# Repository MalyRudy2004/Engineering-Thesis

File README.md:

# Development of a fiber optic system for spatial localization of a person in a room

### Engineering Thesis
**Author:** Piotr Łuczak  
**Student ID:** 246965  
 
---

## 📄 Full Text / Thesis Document
The complete text of the engineering thesis (PDF) can be downloaded here:
[Piotr_Łuczak_Development_of_a_fiber_optic_system_for_spatial_localization_of_a_person_in_a_room.pdf](Piotr_Łuczak_Development_of_a_fiber_optic_system_for_spatial_localization_of_a_person_in_a_room.pdf)

---

## Project Overview
This repository contains all the necessary files to understand, recreate, and further develop the project presented in the engineering thesis. The system utilizes fiber-optic microbending sensors to detect and localize human presence in a room.

## Repository Contents

The repository is organized into the following main sections:

- **Python Application** PC software for real-time visualization of the object's position (GUI).

- **STM32 Firmware** Full `STM32CubeIDE` project for the **STM32F303K8** microcontroller. Contains source code, drivers, and logic implementation.

- **KiCad Design Files** Complete hardware design including:
  - Schematics (`.kicad_sch`)
  - PCB Layout (`.kicad_pcb`)
  - **Component Libraries:** Project-specific schematic symbols, footprints, and 3D models of the components used.

- **Datasheets** Technical documentation for key components used in the project (Laser Drivers, MOSFETs, Photodiodes, etc.).

---

## Important Hardware Disclaimer

**Please read before reproducing the PCB:**

There is a discrepancy in the STM32 pin connections between the KiCad schematics and the STM32CubeIDE project configuration. 

- The connection on the physical PCB was **corrected manually after production** (hardware patch).
- **The correct pinout** is defined and explained in the STM32 Project source code.
- Please refer specifically to the **GPIO library header file** for the verified and working pin configuration.

---
*Politechnika Łódzka (Lodz University of Technology) - 2026*

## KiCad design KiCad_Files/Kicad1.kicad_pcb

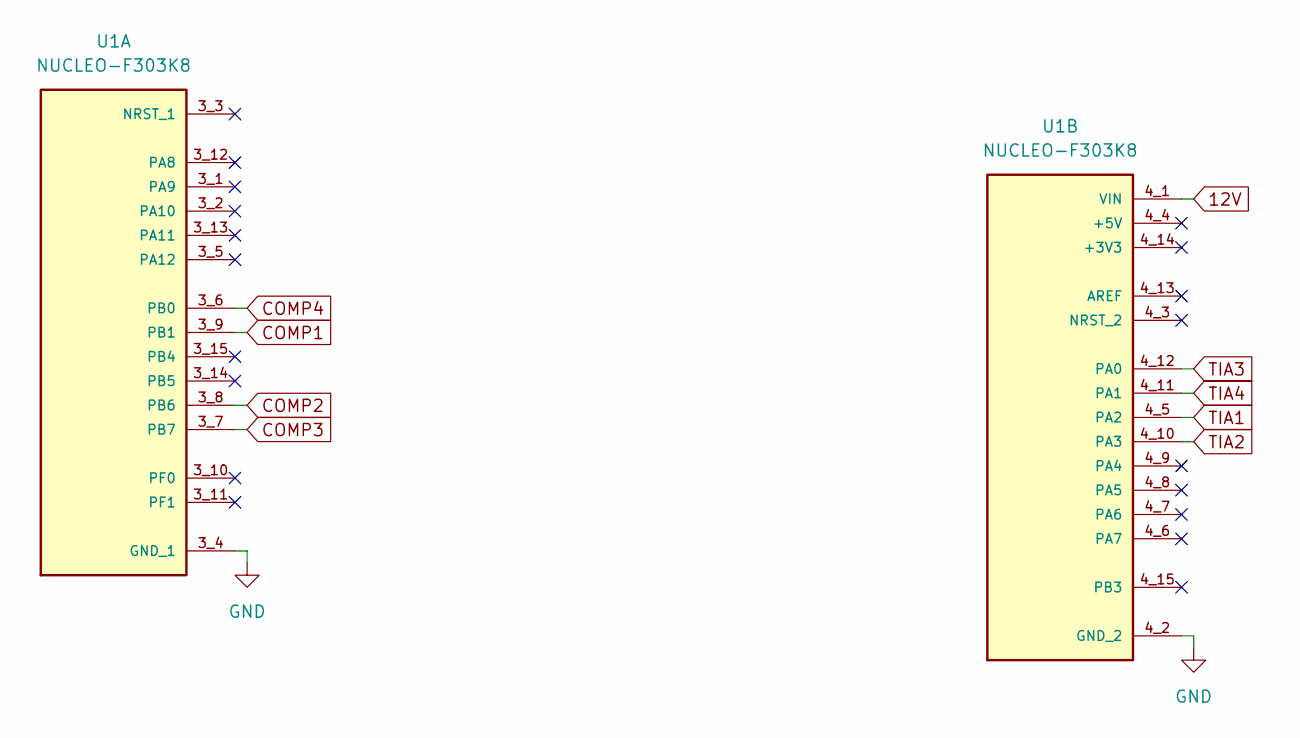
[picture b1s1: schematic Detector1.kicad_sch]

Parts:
U1: NUCLEO-F303K8; MODULE_NUCLEO-F303K8; PARTREV 5

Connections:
12V: U1.4_1 (VIN); also elsewhere on the board
COMP1: U1.3_9 (PB1); also elsewhere on the board
COMP2: U1.3_8 (PB6); also elsewhere on the board
COMP3: U1.3_7 (PB7); also elsewhere on the board
COMP4: U1.3_6 (PB0); also elsewhere on the board
GND: U1.3_4 (GND_1), U1.4_2 (GND_2); also elsewhere on the board
TIA1: U1.4_5 (PA2); also elsewhere on the board
TIA2: U1.4_10 (PA3); also elsewhere on the board
TIA3: U1.4_12 (PA0); also elsewhere on the board
TIA4: U1.4_11 (PA1); also elsewhere on the board

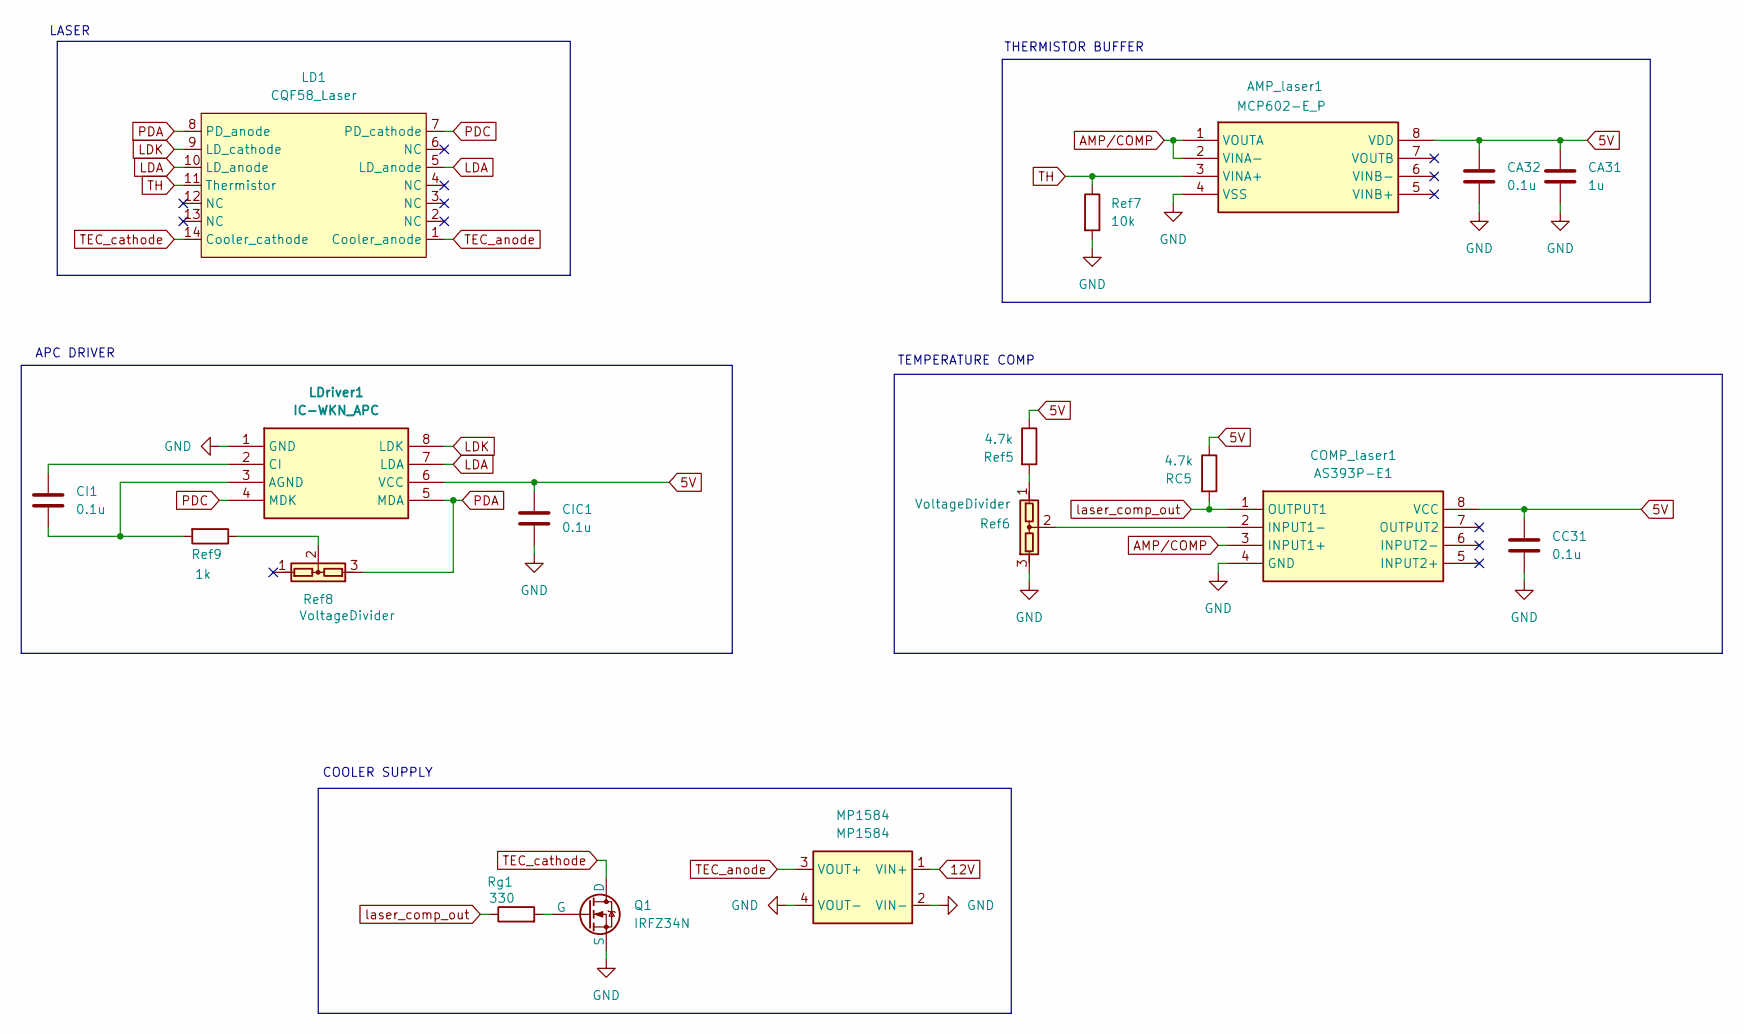
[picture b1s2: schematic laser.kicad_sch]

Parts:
AMP_laser1: MCP602-E_P; DIP781W56P254L950H533Q8N; Manufacturer_Part_Number MCP602-E/P; Mouser Part Number 579-MCP602-E/P
CA31: 1u; C_Radial_D5.0mm_H11.0mm_P2.00mm
CA32: 0.1u; C_Disc_D5.0mm_W2.5mm_P2.50mm
CC31: 0.1u; C_Disc_D5.0mm_W2.5mm_P2.50mm
CI1: 0.1u; C_Disc_D5.0mm_W2.5mm_P2.50mm
CIC1: 0.1u; C_Disc_D5.0mm_W2.5mm_P2.50mm
COMP_laser1: AS393P-E1; DIP762W56P254L930H431Q8N; Manufacturer_Part_Number AS393P-E1; Mouser Part Number 621-AS393P-E1
LD1: CQF58_Laser; CQ58F
LDriver1: IC-WKN_APC; IC-wkn; Manufacturer_Part_Number IC-WKNSOP8
MP1584: MP1584; mp1584
Q1: IRFZ34N
RC5: 4.7k; R_Axial_DIN0207_L6.3mm_D2.5mm_P10.16mm_Horizontal
Ref5: 4.7k; R_Axial_DIN0207_L6.3mm_D2.5mm_P10.16mm_Horizontal
Ref6, Ref8: VoltageDivider; Potentiometer_ACP_CA9-V10_Vertical
Ref7: 10k; R_Axial_DIN0207_L6.3mm_D2.5mm_P10.16mm_Horizontal
Ref9: 1k; R_Axial_DIN0207_L6.3mm_D2.5mm_P10.16mm_Horizontal
Rg1: 330; R_Axial_DIN0207_L6.3mm_D2.5mm_P10.16mm_Horizontal

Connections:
5V: AMP_laser1.8 (VDD), CA31.1, CA32.1, CC31.1, CIC1.1, COMP_laser1.8 (VCC), LDriver1.6 (VCC), RC5.1, Ref5.1; also elsewhere on the board
12V: MP1584.1 (VIN+); also elsewhere on the board
AMP/COMP: AMP_laser1.1 (VOUTA), AMP_laser1.2 (VINA-), COMP_laser1.3 (INPUT1+)
GND: AMP_laser1.4 (VSS), CA31.2, CA32.2, CC31.2, CIC1.2, COMP_laser1.4 (GND), LDriver1.1 (GND), MP1584.2 (VIN-), MP1584.4 (VOUT-), Q1.3 (S), Ref6.3, Ref7.2; also elsewhere on the board
LDA: LD1.5 (LD_anode), LD1.10 (LD_anode), LDriver1.7 (LDA)
LDK: LD1.9 (LD_cathode), LDriver1.8 (LDK)
unnamed: COMP_laser1.2 (INPUT1-), Ref6.2
unnamed: CI1.2, LDriver1.3 (AGND), Ref9.2
unnamed: CI1.1, LDriver1.2 (CI)
unnamed: Q1.2 (G), Rg1.2
unnamed: Ref5.2, Ref6.1
unnamed: Ref8.2, Ref9.1
PDA: LD1.8 (PD_anode), LDriver1.5 (MDA), Ref8.3
PDC: LD1.7 (PD_cathode), LDriver1.4 (MDK)
TEC_anode: LD1.1 (Cooler_anode), MP1584.3 (VOUT+)
TEC_cathode: LD1.14 (Cooler_cathode), Q1.1 (D)
TH: AMP_laser1.3 (VINA+), LD1.11 (Thermistor), Ref7.1
laser_comp_out: COMP_laser1.1 (OUTPUT1), RC5.2, Rg1.1

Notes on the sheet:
COOLER SUPPLY
APC DRIVER
TEMPERATURE COMP
LASER
THERMISTOR BUFFER

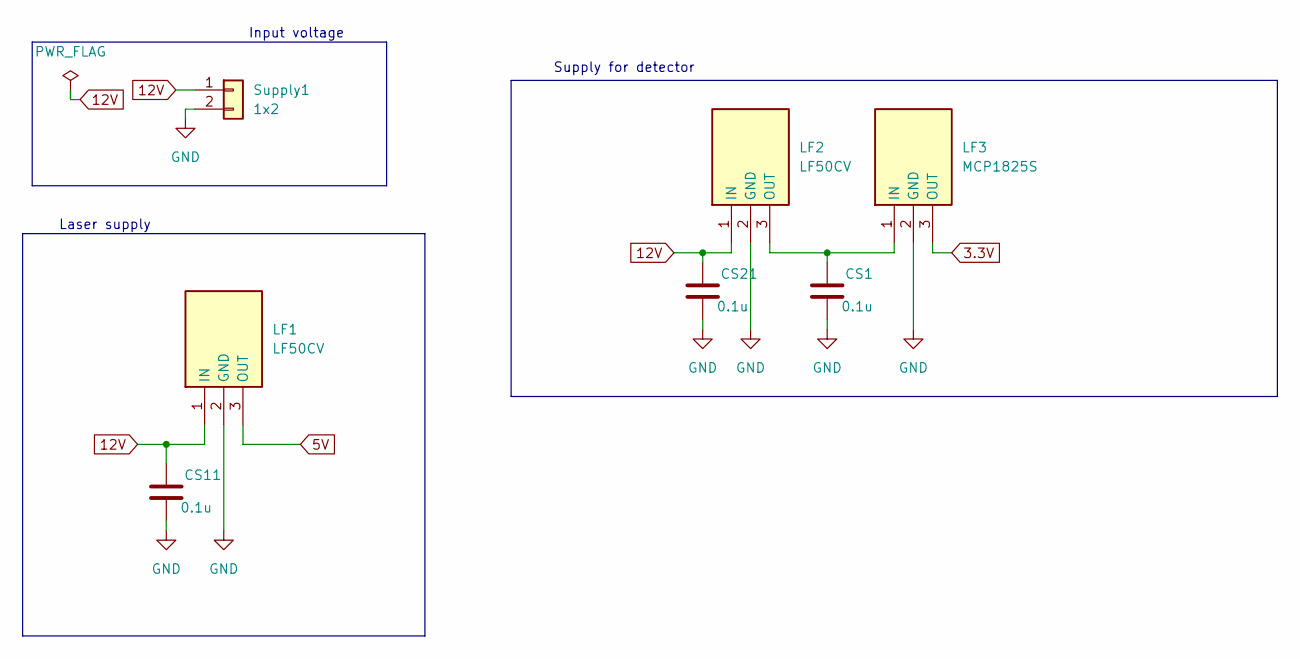
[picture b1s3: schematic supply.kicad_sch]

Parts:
CS1, CS11, CS21: 0.1u; C_Disc_D5.0mm_W2.5mm_P2.50mm
LF1, LF2: LF50CV; TO-220-3_Vertical; Manufacturer_Part_Number LF50CV; Mouser Part Number 511-LF50CV
LF3: MCP1825S; TO-220-3_Vertical; Manufacturer_Part_Number LF50CV; Mouser Part Number 511-LF50CV
Supply1: 1x2; PinHeader_1x02_P2.54mm_Vertical

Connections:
3.3V: LF3.3 (OUT); also elsewhere on the board
5V: LF1.3 (OUT); also elsewhere on the board
12V: CS11.1, CS21.1, LF1.1 (IN), LF2.1 (IN), Supply1.1; also elsewhere on the board
GND: CS1.2, CS11.2, CS21.2, LF1.2 (GND), LF2.2 (GND), LF3.2 (GND), Supply1.2; also elsewhere on the board
unnamed: CS1.1, LF2.3 (OUT), LF3.1 (IN)

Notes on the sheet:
Input voltage
Supply for detector
Laser supply

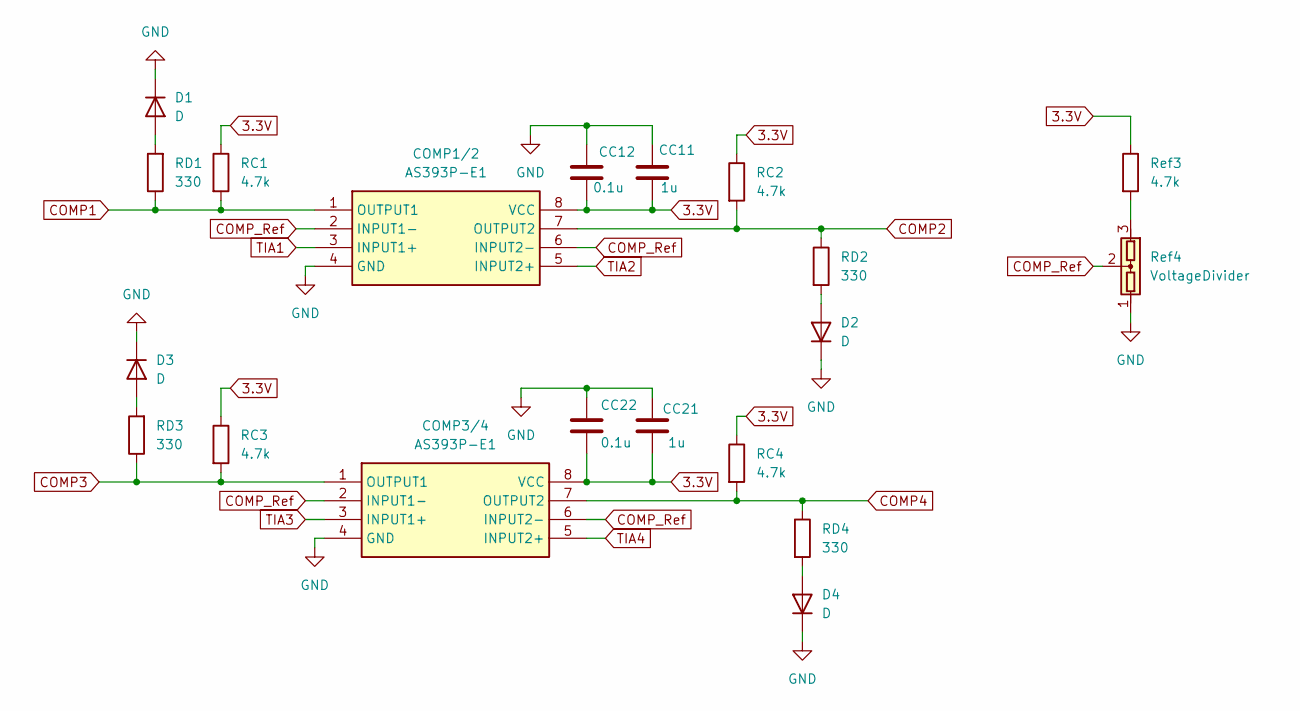
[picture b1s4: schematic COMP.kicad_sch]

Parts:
CC11, CC21: 1u; C_Radial_D5.0mm_H11.0mm_P2.00mm
CC12, CC22: 0.1u; C_Disc_D5.0mm_W2.5mm_P2.50mm
COMP1/2, COMP3/4: AS393P-E1; DIP762W56P254L930H431Q8N; Manufacturer_Part_Number AS393P-E1; Mouser Part Number 621-AS393P-E1
D1, D2, D3, D4: D; LED_D5.0mm
RC1, RC2, RC3, RC4: 4.7k; R_Axial_DIN0207_L6.3mm_D2.5mm_P10.16mm_Horizontal
RD1, RD2, RD3, RD4: 330; R_Axial_DIN0207_L6.3mm_D2.5mm_P10.16mm_Horizontal
Ref3: 4.7k; R_Axial_DIN0207_L6.3mm_D2.5mm_P10.16mm_Horizontal
Ref4: VoltageDivider; Potentiometer_ACP_CA9-V10_Vertical

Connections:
3.3V: CC11.2, CC12.2, CC21.2, CC22.2, COMP1/2.8 (VCC), COMP3/4.8 (VCC), RC1.1, RC2.1, RC3.1, RC4.1, Ref3.1; also elsewhere on the board
COMP1: COMP1/2.1 (OUTPUT1), RC1.2, RD1.1; also elsewhere on the board
COMP2: COMP1/2.7 (OUTPUT2), RC2.2, RD2.1; also elsewhere on the board
COMP3: COMP3/4.1 (OUTPUT1), RC3.2, RD3.1; also elsewhere on the board
COMP4: COMP3/4.7 (OUTPUT2), RC4.2, RD4.1; also elsewhere on the board
COMP_Ref: COMP1/2.2 (INPUT1-), COMP1/2.6 (INPUT2-), COMP3/4.2 (INPUT1-), COMP3/4.6 (INPUT2-), Ref4.2
GND: CC11.1, CC12.1, CC21.1, CC22.1, COMP1/2.4 (GND), COMP3/4.4 (GND), D1.1 (K), D2.1 (K), D3.1 (K), D4.1 (K), Ref4.1; also elsewhere on the board
unnamed: D1.2 (A), RD1.2
unnamed: D2.2 (A), RD2.2
unnamed: D3.2 (A), RD3.2
unnamed: D4.2 (A), RD4.2
unnamed: Ref3.2, Ref4.3
TIA1: COMP1/2.3 (INPUT1+); also elsewhere on the board
TIA2: COMP1/2.5 (INPUT2+); also elsewhere on the board
TIA3: COMP3/4.3 (INPUT1+); also elsewhere on the board
TIA4: COMP3/4.5 (INPUT2+); also elsewhere on the board

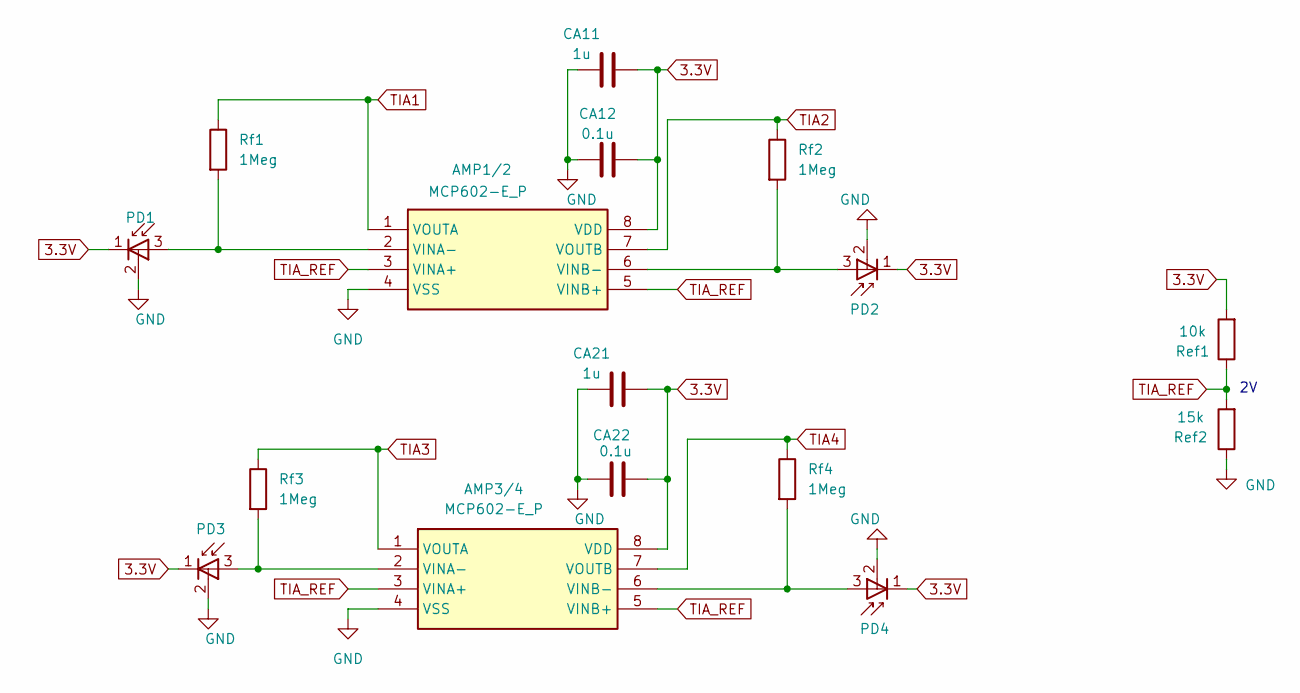
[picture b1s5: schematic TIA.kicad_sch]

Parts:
AMP1/2, AMP3/4: MCP602-E_P; DIP781W56P254L950H533Q8N; Manufacturer_Part_Number MCP602-E/P; Mouser Part Number 579-MCP602-E/P
CA11, CA21: 1u; C_Radial_D5.0mm_H11.0mm_P2.00mm
CA12, CA22: 0.1u; C_Disc_D5.0mm_W2.5mm_P2.50mm
PD1, PD2, PD3, PD4: Fotodiode
Ref1: 10k; R_Axial_DIN0207_L6.3mm_D2.5mm_P10.16mm_Horizontal
Ref2: 15k; R_Axial_DIN0207_L6.3mm_D2.5mm_P10.16mm_Horizontal
Rf1, Rf2, Rf3, Rf4: 1Meg; R_Axial_DIN0207_L6.3mm_D2.5mm_P10.16mm_Horizontal

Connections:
3.3V: AMP1/2.8 (VDD), AMP3/4.8 (VDD), CA11.1, CA12.1, CA21.1, CA22.1, PD1.1, PD2.1, PD3.1, PD4.1, Ref1.2; also elsewhere on the board
GND: AMP1/2.4 (VSS), AMP3/4.4 (VSS), CA11.2, CA12.2, CA21.2, CA22.2, PD1.2, PD2.2, PD3.2, PD4.2, Ref2.1; also elsewhere on the board
unnamed: AMP1/2.2 (VINA-), PD1.3, Rf1.2
unnamed: AMP1/2.6 (VINB-), PD2.3, Rf2.2
unnamed: AMP3/4.2 (VINA-), PD3.3, Rf3.2
unnamed: AMP3/4.6 (VINB-), PD4.3, Rf4.2
TIA1: AMP1/2.1 (VOUTA), Rf1.1; also elsewhere on the board
TIA2: AMP1/2.7 (VOUTB), Rf2.1; also elsewhere on the board
TIA3: AMP3/4.1 (VOUTA), Rf3.1; also elsewhere on the board
TIA4: AMP3/4.7 (VOUTB), Rf4.1; also elsewhere on the board
TIA_REF: AMP1/2.3 (VINA+), AMP1/2.5 (VINB+), AMP3/4.3 (VINA+), AMP3/4.5 (VINB+), Ref1.1, Ref2.2

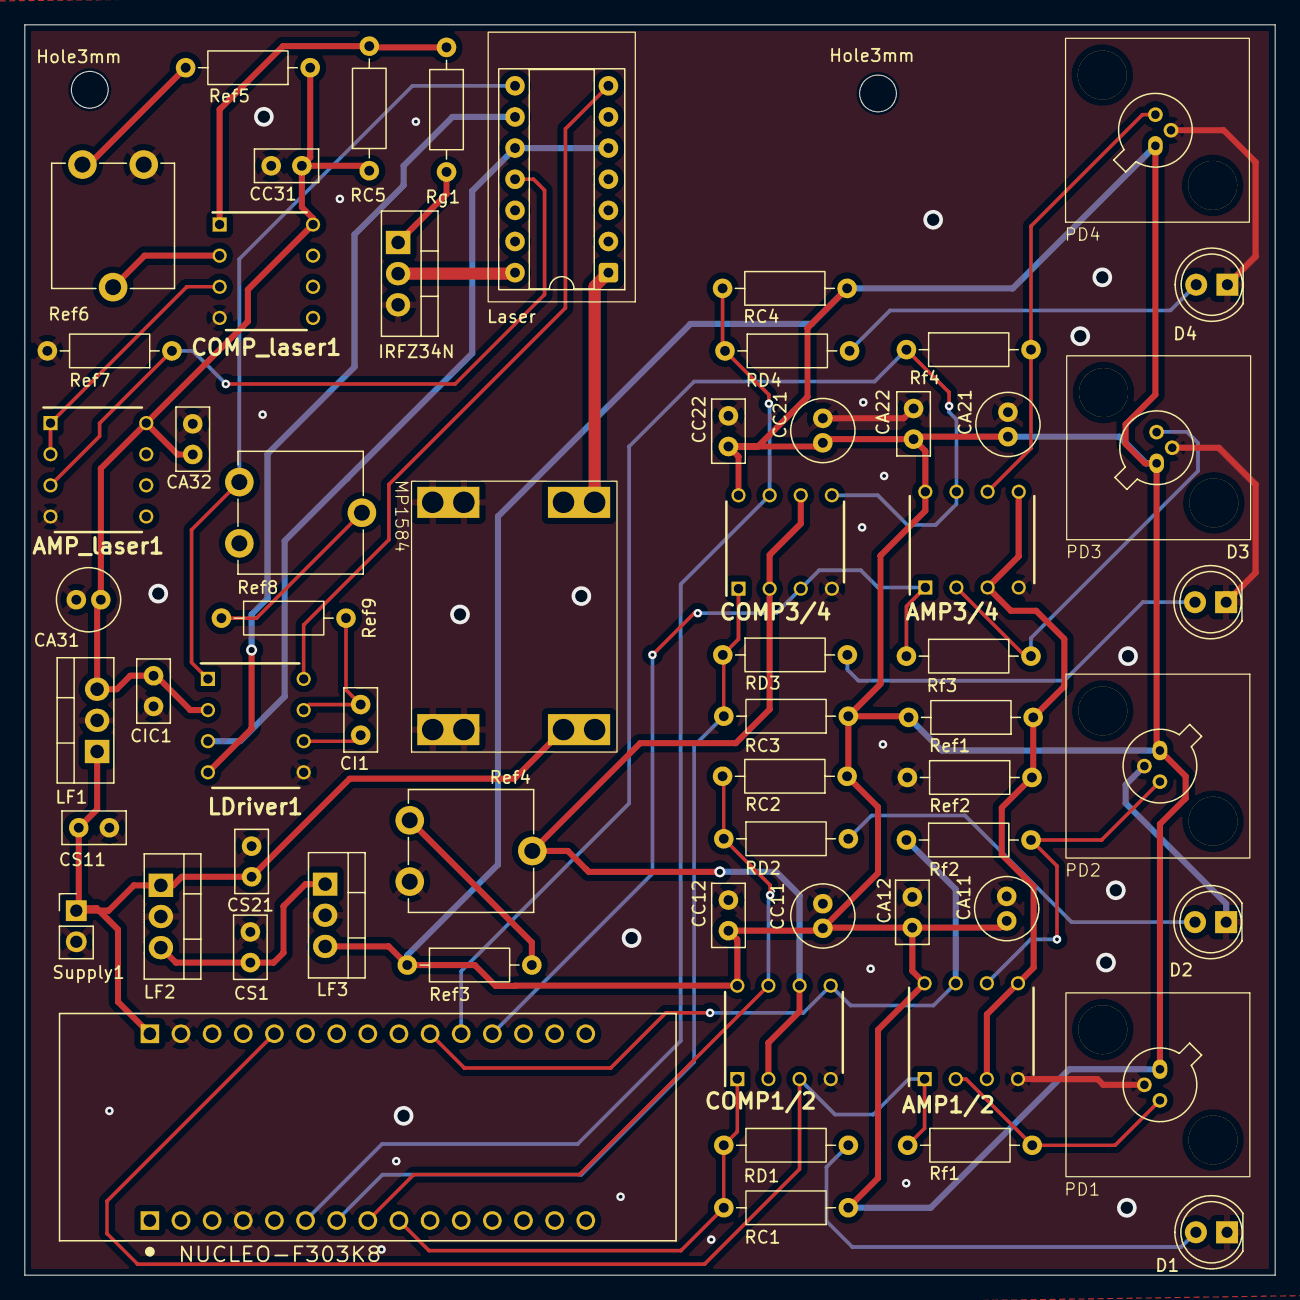
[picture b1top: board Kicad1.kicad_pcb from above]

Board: 2 copper layers, 102.0 x 102.0 mm, 62 parts (0 on the bottom side), 39 nets.

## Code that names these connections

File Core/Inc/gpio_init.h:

/*
 * gpio_init.h
 *
 *  Created on: Oct 14, 2025
 *      Author: malyrudy
 */

#ifndef INC_GPIO_INIT_H_
#define INC_GPIO_INIT_H_

#include "main.h"
#include "stm32f303x8.h"


typedef enum MODER {
	INPUT = 0x0,
	OUTPUT = 0x1,
	ALTERNATE = 0x2,
	ANALOG = 0x3
}MODER;

typedef enum OTYPER {
	PUSHPULL = 0x0,
	OPENDRAIN = 0x1
}OTYPER;

typedef enum OSPEEDR {
	LOW = 0x0,
	MEDIUM = 0x1,
	HIGH = 0x3
}OSPEEDR;

typedef enum PUPDR {
	NOPULL = 0x0,
	PULLUP = 0x1,
	PULLDOWN = 0x2
}PUPDR;

typedef enum STATE{
	OFF = 0x0,
	ON = 0x1
}STATE;


void clock_enable();
void gpio_init(GPIO_TypeDef *port, uint8_t pin, enum MODER mode, enum OTYPER type, enum OSPEEDR speed, enum PUPDR pupd);

// -------------------------------------------------- COMPARATORS
// -------------------------------------------------- PB1 COMP1
// -------------------------------------------------- PB6 COMP2
// -------------------------------------------------- PB7 COMP3
// -------------------------------------------------- PB0 COMP4
#define COMP1pin 1
#define COMP1mask (1 << COMP1pin)
#define COMP2pin 6
#define COMP2mask (1 << COMP2pin)
#define COMP3pin 7
#define COMP3mask (1 << COMP3pin)
#define COMP4pin 0
#define COMP4mask (1 << COMP4pin)
void gpio_comp_init();

// -------------------------------------------------- ANALOG TO DIGITAL CONVERTER
// -------------------------------------------------- PA2 ADC1 -- wrong, vcp conected here, reschedule manualy for PA7	//ADC2 IN4
// -------------------------------------------------- PA3 ADC2 -- reschedule it for PA4 for balance						//ADC2 IN1
// -------------------------------------------------- PA0 ADC3															//ADC1 IN1
// -------------------------------------------------- PA1 ADC4															//ADC1 IN2
#define ADC1pin 7
#define ADC2pin 4
#define ADC3pin 0
#define ADC4pin 1
void gpio_adc_init();

// -------------------------------------------------- USART TO PC
// -------------------------------------------------- PA2 VCP_TX
// -------------------------------------------------- PA15 VCP_RX
#define USARTTXpin 2
#define USARTRXpin 15
#define AF7 0b0111
void gpio_usart_init();

#endif /* INC_GPIO_INIT_H_ */

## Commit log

2026-01-23 stm32project
2026-01-23 poprawki
2026-01-23 Dodanie duzych datasheetow
